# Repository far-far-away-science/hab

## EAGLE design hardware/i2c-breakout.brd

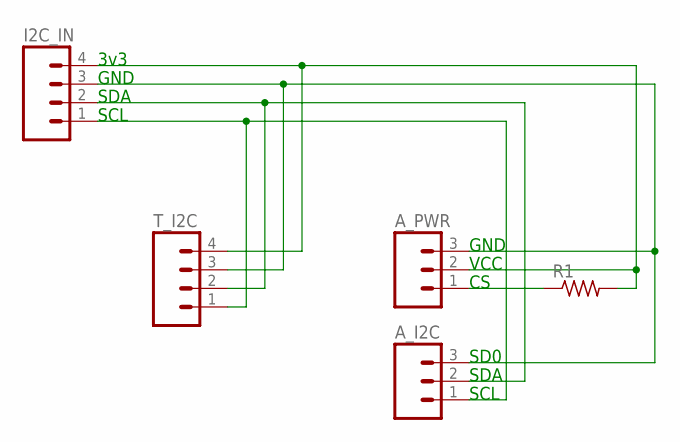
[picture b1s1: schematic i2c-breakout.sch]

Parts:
A_I2C: M03PTH; 1X03
A_PWR: M03PTH; 1X03
I2C_IN: M04PTH; 1X04
R1: R-US_0207/7; 0207/7
T_I2C: M04PTH; 1X04

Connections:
3V3: A_PWR.2, I2C_IN.4, R1.2, T_I2C.4
CS: A_PWR.1, R1.1
GND: A_I2C.3, A_PWR.3, I2C_IN.3, T_I2C.3
SCL: A_I2C.1, I2C_IN.1, T_I2C.1
SDA: A_I2C.2, I2C_IN.2, T_I2C.2

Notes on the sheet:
SCL
SDA
GND
3v3
SD0
VCC

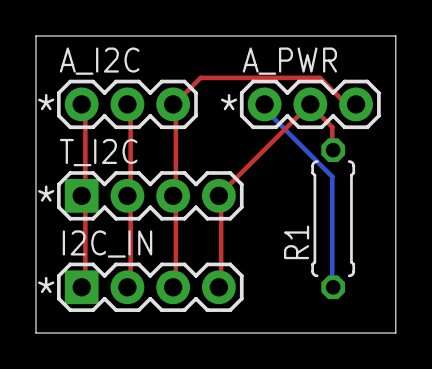
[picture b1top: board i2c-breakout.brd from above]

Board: 2 copper layers, 20.0 x 16.5 mm, 5 parts (0 on the bottom side), 5 nets.

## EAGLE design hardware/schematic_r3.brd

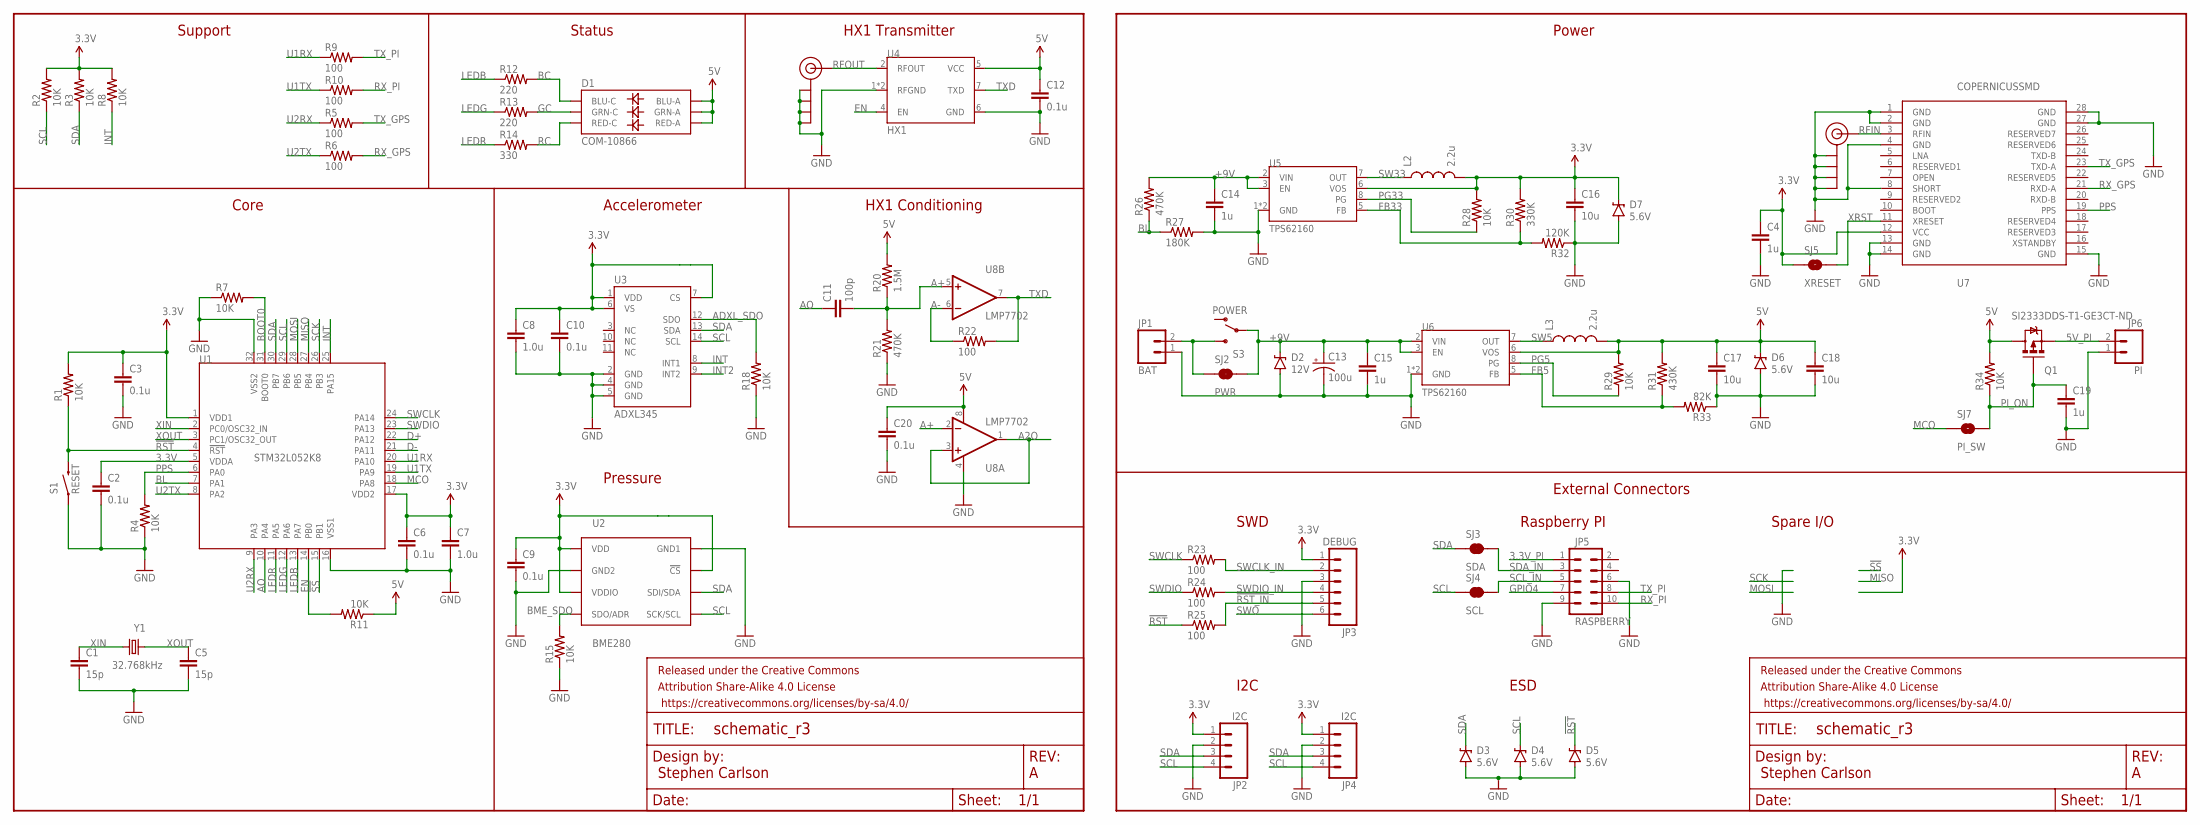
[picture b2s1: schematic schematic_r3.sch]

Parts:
C1, C5: 15p; 0805
C2, C3, C6, C9, C10, C12, C20: 0.1u; 0805
C4, C14, C15, C19: 1u; 0805
C7, C8: 1.0u; 0805
C11: 100p; 0805
C13: 100u; CPOL-RADIAL-10UF-25V
C16, C17, C18: 10u; 0805
D1: COM-10866; LED-TRICOLOR-5050
D2: 12V; SOD-323
D3, D4, D5, D6, D7: 5.6V; SOD-323
FRAME1, FRAME2: FRAME-LETTERNO_PACKAGE; DUMMY
J$1, J$2: SMA_EDGE; SMA-EDGE
JP1: BAT; 1X02
JP2, JP4: I2C; 1X04_LOCK
JP3: DEBUG; 1X06_LOCK
JP5: RASPBERRY; AVR_ICSP
JP6: PI; 1X02
L2, L3: 2.2u; 1008
Q1: SI2333DDS-T1-GE3CT-ND; SOT23-3
R1, R2, R3, R4, R7, R8, R11, R15, R18, R28, R29, R34: 10K; 0805
R5, R6, R9, R10, R22, R23, R24, R25: 100; 0805
R12, R13: 220; 0805
R14: 330; 0805
R20: 1.5M; 0805
R21, R26: 470K; 0805
R27: 180K; 0805
R30: 330K; 0805
R31: 430K; 0805
R32: 120K; 0805
R33: 82K; 0805
S1: RESET; TACTILE-PTH-THIN
S3: POWER; SWITCH-SPDT
SJ2: PWR; PAD-JUMPER-2-NC_BY_TRACE_YES_SILK
SJ3: SDA; PAD-JUMPER-2-NC_BY_TRACE_YES_SILK
SJ4: SCL; PAD-JUMPER-2-NC_BY_TRACE_YES_SILK
SJ5: XRESET; PAD-JUMPER-2-NO_YES_SILK
SJ7: PI_SW; PAD-JUMPER-2-NO_YES_SILK
U1: STM32L052K8; TQFP32-08
U2: BME280; BME280_LGA
U3: ADXL345; LGA14
U4: HX1; 1X12
U5, U6: TPS62160; MSOP8
U7: COPERNICUSSMD; COPERNICUS
U8: LMP7702; SO08
Y1: 32.768kHz; ABS25

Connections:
3.3V: C2.1, C3.1, C4.1, C6.1, C7.1, C8.1, C9.1, C10.1, C16.1, D7.C, JP2.1, JP3.1, JP4.1, L2.2, R1.2, R2.2, R3.2, R8.2, R28.2, R30.2, SJ5.1, U1.1 (VDD1), U1.5 (VDDA), U1.17 (VDD2), U2.P$2 (!CS), U2.P$6 (VDDIO), U2.P$8 (VDD), U3.1 (VDD), U3.6 (VS), U3.7 (CS), U5.6 (VOS), U7.12 (VCC)
3.3V_PI: JP5.1
5V: C12.1, C17.1, C18.1, C20.1, D1.1 (GRN-A), D1.2 (RED-A), D1.3 (BLU-A), D6.C, L3.2, Q1.3 (D), R11.1, R20.2, R29.2, R31.2, R34.2, U4.5 (VCC), U6.6 (VOS), U8.8 (V+)
5V_PI: JP6.2, Q1.2 (S)
!RST!: D5.C, R1.1, R25.1, S1.2, U1.4 (!RST!)
!RST_IN!: JP3.5, R25.2
!SS!: U1.15 (PB1)
+9V: C13.1 (+), C14.1, C15.1, D2.C, R26.2, S3.2, SJ2.2, U5.2 (VIN), U5.3 (EN), U6.2 (VIN), U6.3 (EN)
A2O: U8.1 (OUT), U8.3 (+IN)
A+: C11.2, R20.1, R21.2, U8.2 (-IN), U8.5 (+IN)
A-: R22.1, U8.6 (-IN)
ADXL_SDO: R18.2, U3.12 (SDO)
AO: C11.1, U1.10 (PA4)
BC: D1.4 (BLU-C), R12.2
BL: R26.1, R27.1, U1.7 (PA1)
BME_SDO: R15.2, U2.P$5 (SDO/ADR)
BOOT0: R7.2, U1.31 (BOOT0)
D+: U1.22 (PA12)
D-: U1.21 (PA11)
EN: R11.2, U1.14 (PB0), U4.4 (EN)
FB5: R31.1, R33.2, U6.5 (FB)
FB33: R30.1, R32.2, U5.5 (FB)
GC: D1.6 (GRN-C), R13.2
GND: C1.2, C2.2, C3.2, C4.2, C5.2, C6.2, C7.2, C8.2, C9.2, C10.2, C12.2, C13.2 (-), C14.2, C15.2, C16.2, C17.2, C18.2, C19.2, C20.2, D2.A, D3.A, D4.A, D5.A, D6.A, D7.A, J$1.GND@0 (GND), J$1.GND@1 (GND), J$1.GND@2 (GND), J$1.GND@3 (GND), J$2.GND@0 (GND), J$2.GND@1 (GND), J$2.GND@2 (GND), J$2.GND@3 (GND), JP1.1, JP2.2, JP3.3, JP4.2, JP5.6, JP5.9, JP6.1, R4.1, R7.1, R15.1, R18.1, R21.1, R27.2, R32.1, R33.1, S1.1, U1.16 (VSS1), U1.32 (VSS2), U2.P$1 (GND1), U2.P$7 (GND2), U3.2 (GND), U3.4 (GND), U3.5 (GND), U4.1 (RFGND), U4.3 (RFGND), U4.6 (GND), U5.1 (GND), U5.4 (GND), U6.1 (GND), U6.4 (GND), U7.1 (GND), U7.2 (GND), U7.4 (GND), U7.8 (SHORT), U7.13 (GND), U7.14 (GND), U7.15 (GND), U7.27 (GND), U7.28 (GND), U8.4 (V-)
GPIO4: JP5.7
INT: R8.1, U1.25 (PA15), U3.8 (INT1)
INT2: U3.9 (INT2)
LEDB: R12.1, U1.13 (PA7)
LEDG: R13.1, U1.12 (PA6)
LEDR: R14.1, U1.11 (PA5)
MCO: SJ7.1, U1.18 (PA8)
MISO: U1.27 (PB4)
MOSI: U1.28 (PB5)
PG5: R29.1, U6.8 (PG)
PG33: R28.1, U5.8 (PG)
PI_ON: C19.1, Q1.1 (G), R34.1, SJ7.2
PPS: R4.2, U1.6 (PA0), U7.19 (PPS)
RC: D1.5 (RED-C), R14.2
RFIN: J$2.SIG (SIGNAL), U7.3 (RFIN)
RFOUT: J$1.SIG (SIGNAL), U4.2 (RFOUT)
RX_GPS: R6.2, U7.21 (RXD-A)
RX_PI: JP5.10, R10.2
SCK: U1.26 (PB3)
SCL: D4.C, JP2.4, JP4.4, R2.1, SJ4.1, U1.29 (PB6), U2.P$4 (SCK/SCL), U3.14 (SCL)
SCL_IN: JP5.5, SJ4.2
SDA: D3.C, JP2.3, JP4.3, R3.1, SJ3.1, U1.30 (PB7), U2.P$3 (SDI/SDA), U3.13 (SDA)
SDA_IN: JP5.3, SJ3.2
SW5: L3.1, U6.7 (OUT)
SW33: L2.1, U5.7 (OUT)
SWCLK: R23.1, U1.24 (PA14)
SWCLK_IN: JP3.2, R23.2
SWDIO: R24.1, U1.23 (PA13)
SWDIO_IN: JP3.4, R24.2
SWO: JP3.6
TXD: R22.2, U4.7 (TXD), U8.7 (OUT)
TX_GPS: R5.2, U7.23 (TXD-A)
TX_PI: JP5.8, R9.2
U1RX: R9.1, U1.20 (PA10)
U1TX: R10.1, U1.19 (PA9)
U2RX: R5.1, U1.9 (PA3)
U2TX: R6.1, U1.8 (PA2)
VIN: JP1.2, S3.3 (S), SJ2.1
XIN: C1.1, U1.2 (PC0/OSC32_IN), Y1.1
XOUT: C5.1, U1.3 (PC1/OSC32_OUT), Y1.4 (2)
XRST: SJ5.2, U7.11 (XRESET)

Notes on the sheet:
Stephen Carlson
External Connectors
SWD
Raspberry PI
Spare I/O
Support
Status
HX1 Transmitter
Core
Accelerometer
Pressure
HX1 Conditioning
I2C
ESD
Power

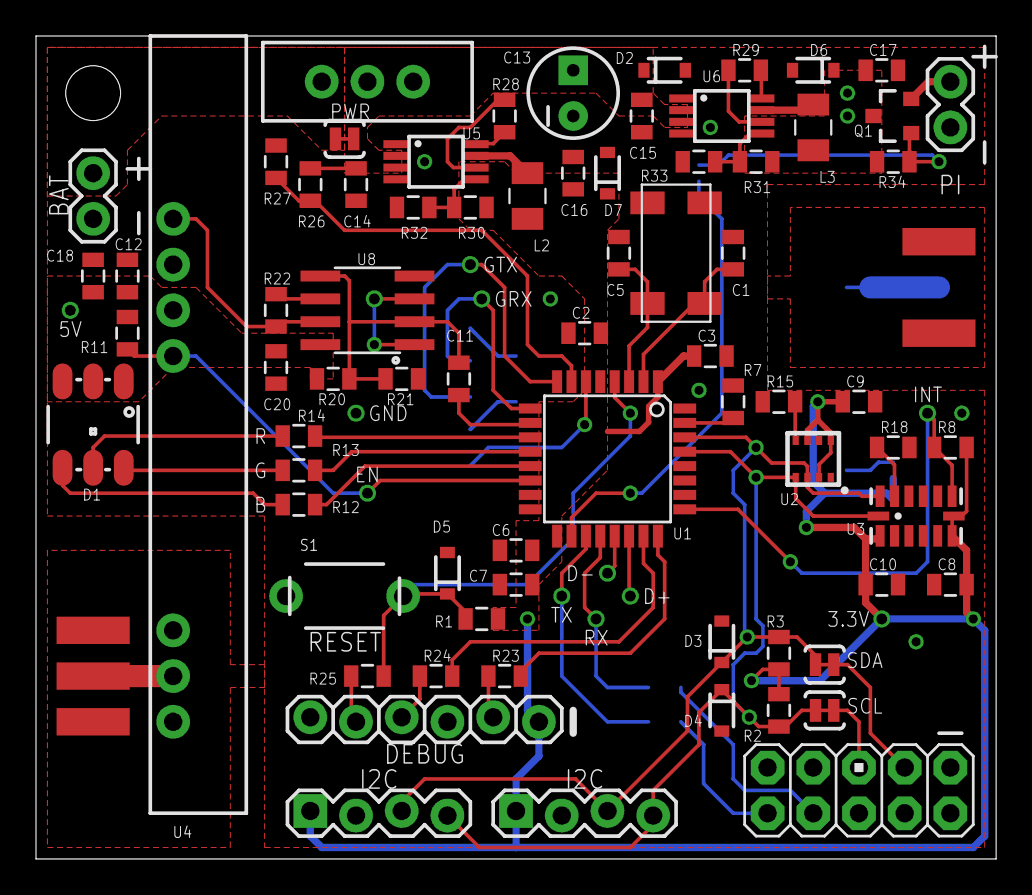
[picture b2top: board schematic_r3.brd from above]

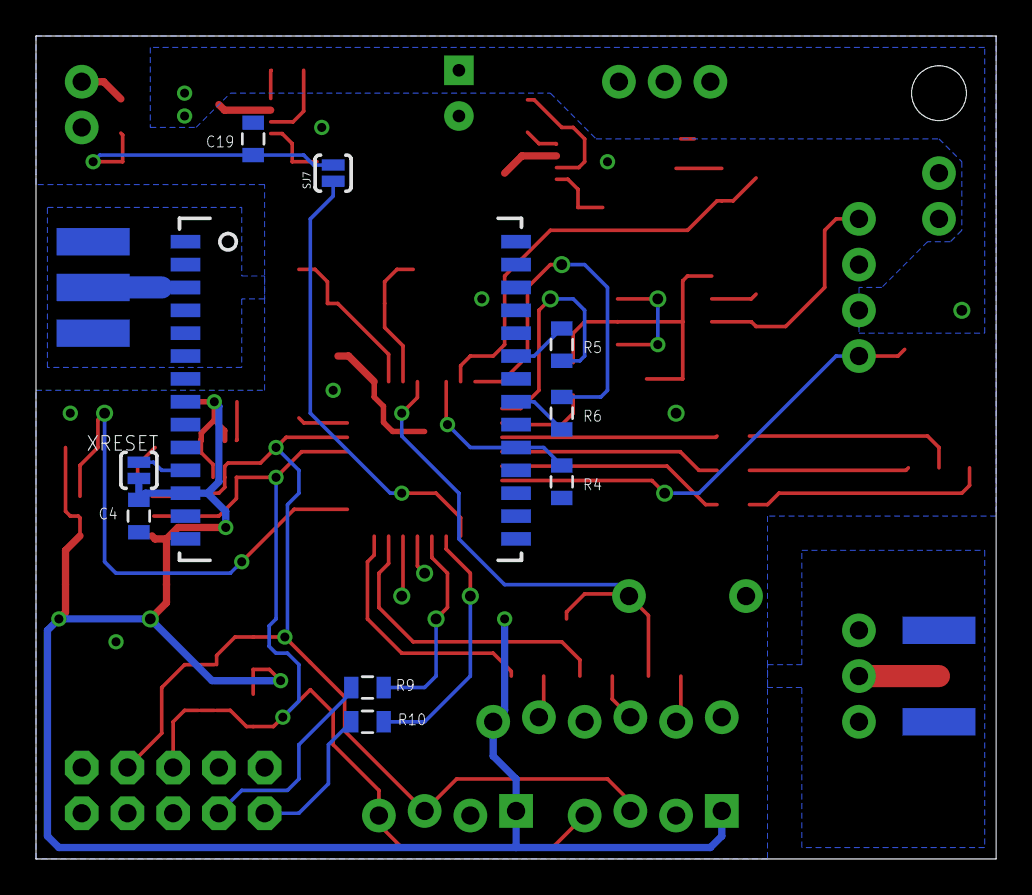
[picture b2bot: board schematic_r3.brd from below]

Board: 2 copper layers, 53.3 x 45.7 mm, 87 parts (11 on the bottom side), 55 nets.

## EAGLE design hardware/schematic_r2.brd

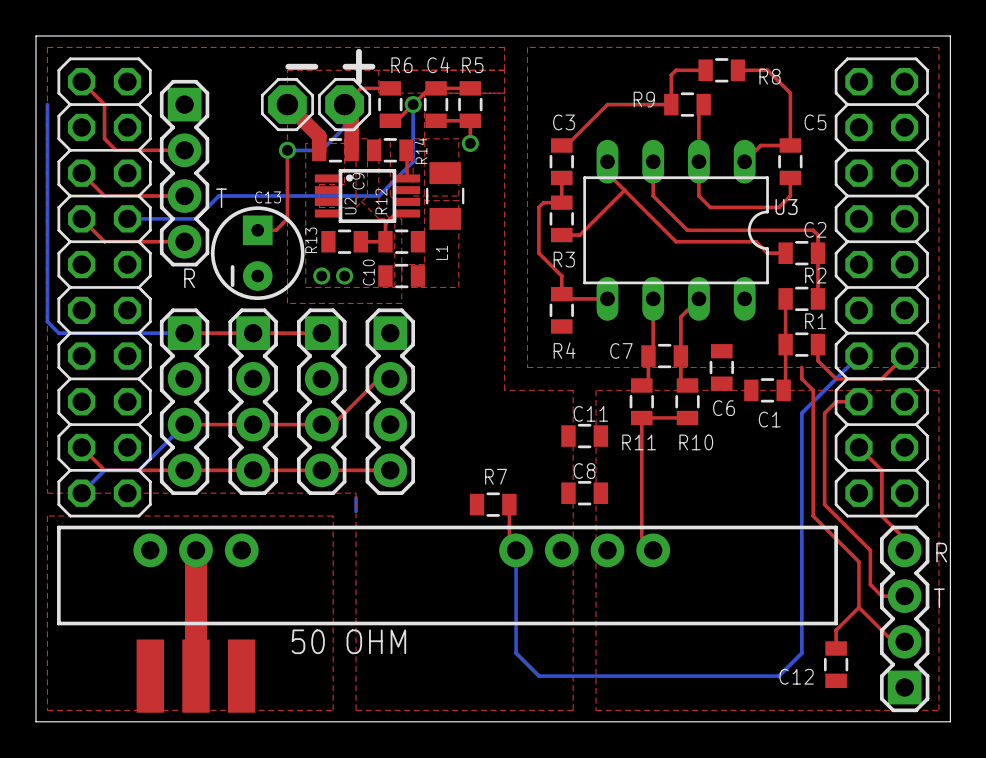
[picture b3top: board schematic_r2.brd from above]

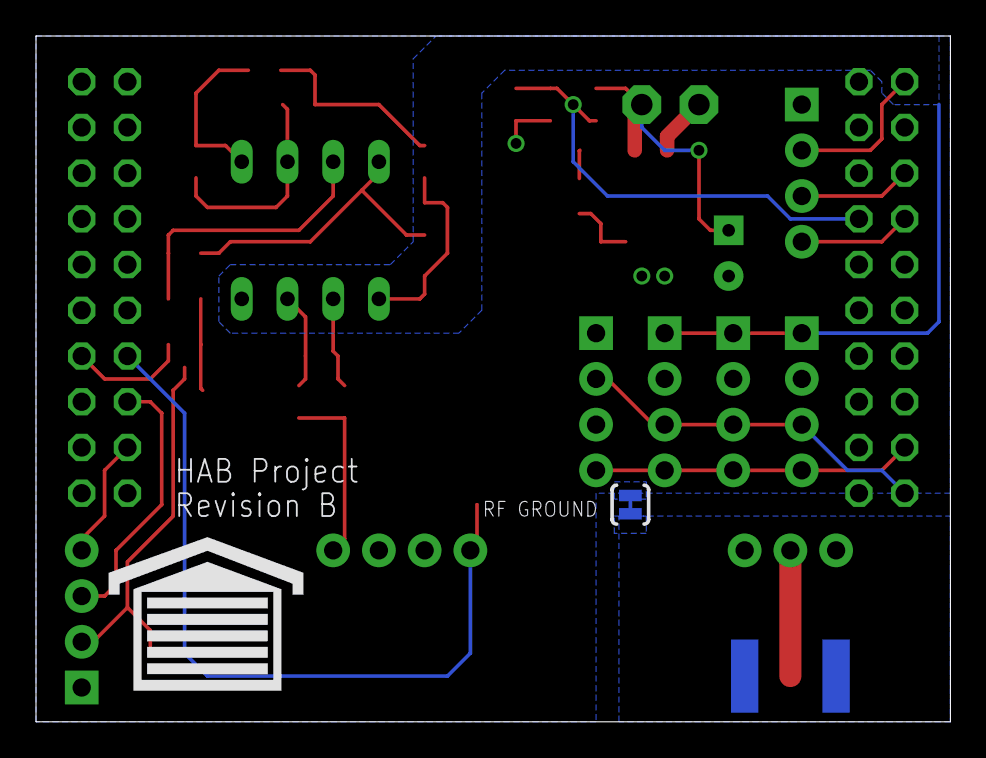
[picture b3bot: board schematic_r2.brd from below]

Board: 2 copper layers, 50.8 x 38.1 mm, 45 parts (2 on the bottom side), 27 nets.

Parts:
C1: 47nF; 0805
C2, C3: 100pF; 0805
C4, C6, C8, C12: 0.1uF; 0805
C5, C7: 10pF; 0805
C9, C10, C11: 10u; 0805
C13: 68u; CPOL-RADIAL-10UF-25V
FRAME1: FRAME-LETTERNO_PACKAGE; DUMMY
J1: SMA_EDGE; SMA-EDGE
JP1: I2C IN; 1X04
JP2, JP5, JP6: SENSORS; 1X04
JP3: VENUS; 1X04
JP4: COPERNICUS; 1X04
L1: 2.2u; 1008
R1: 1K; 0805
R2, R3, R6: 470K; 0805
R4: 1.5M; 0805
R5: 180K; 0805
R7: 2.2K; 0805
R8, R10: 100; 0805
R9, R11, R14: 100K; 0805
R12: 430K; 0805
R13: 82K; 0805
SJ1: JUMPER-PAD-2-NC_BY_TRACE; PAD-JUMPER-2-NC_BY_TRACE_YES_SILK
TIVA_1, TIVA_2: 2X10
TP1, TP2: MCS08
U1: HX1; 1X12
U2: TPS62160; MSOP8
U3: LMC6482; DIL08
U$1: GARAGE

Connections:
+3V3: C6.1, C12.1, JP2.1, JP3.2, JP4.2, JP5.1, JP6.1, R4.2, TIVA_1.1, U3.8
+5V: C8.1, C10.1, C11.1, JP1.1, L1.2, R7.2, R12.2, R14.2, TIVA_1.2, U1.5, U2.6
+9V: C9.1, C13.1, R6.2, TP1.MP, U2.2, U2.3
CRX: JP4.4, TIVA_2.17
CTX: JP4.3, TIVA_2.15
EN: R7.1, TIVA_2.13, U1.4
FB5: R12.1, R13.2, U2.5
GNDA: C1.2, C2.2, C4.2, C6.2, C8.2, C9.2, C10.2, C11.2, C12.2, C13.2, JP1.3, JP2.2, JP3.1, JP4.1, JP5.2, JP6.2, R3.1, R5.1, R13.1, SJ1.1, TIVA_1.4, TIVA_2.2, TP2.MP, U1.6, U2.1, U2.4, U3.4
HPFB: C7.2, R11.1, U3.6
HPIN: C3.1, R8.2, R9.2
HPOUT: C3.2, R3.2, R4.1, U3.5
LPFB: C5.2, R9.1, U3.2
LPOUT: C5.1, R8.1, U3.1
PG5: R14.1, U2.8
PWMF1: C1.1, R1.2, R2.1
PWMF2: C2.1, R2.2, U3.3
PWMOUT: R1.1, TIVA_2.14
RFGND: J1.GND@0, J1.GND@1, J1.GND@2, J1.GND@3, SJ1.2, U1.1, U1.3
RFOUT: J1.SIG, U1.2
SCL: JP1.4, JP2.4, JP5.4, JP6.4, TIVA_1.17
SDA: JP1.2, JP2.3, JP5.3, JP6.3, TIVA_1.19
SW5: L1.1, U2.7
TXD: R10.2, R11.2, U1.7
TXF: C7.1, R10.1, U3.7
VBAT: C4.1, R5.2, R6.1, TIVA_1.8
VRX: JP3.4, TIVA_1.7
VTX: JP3.3, TIVA_1.5

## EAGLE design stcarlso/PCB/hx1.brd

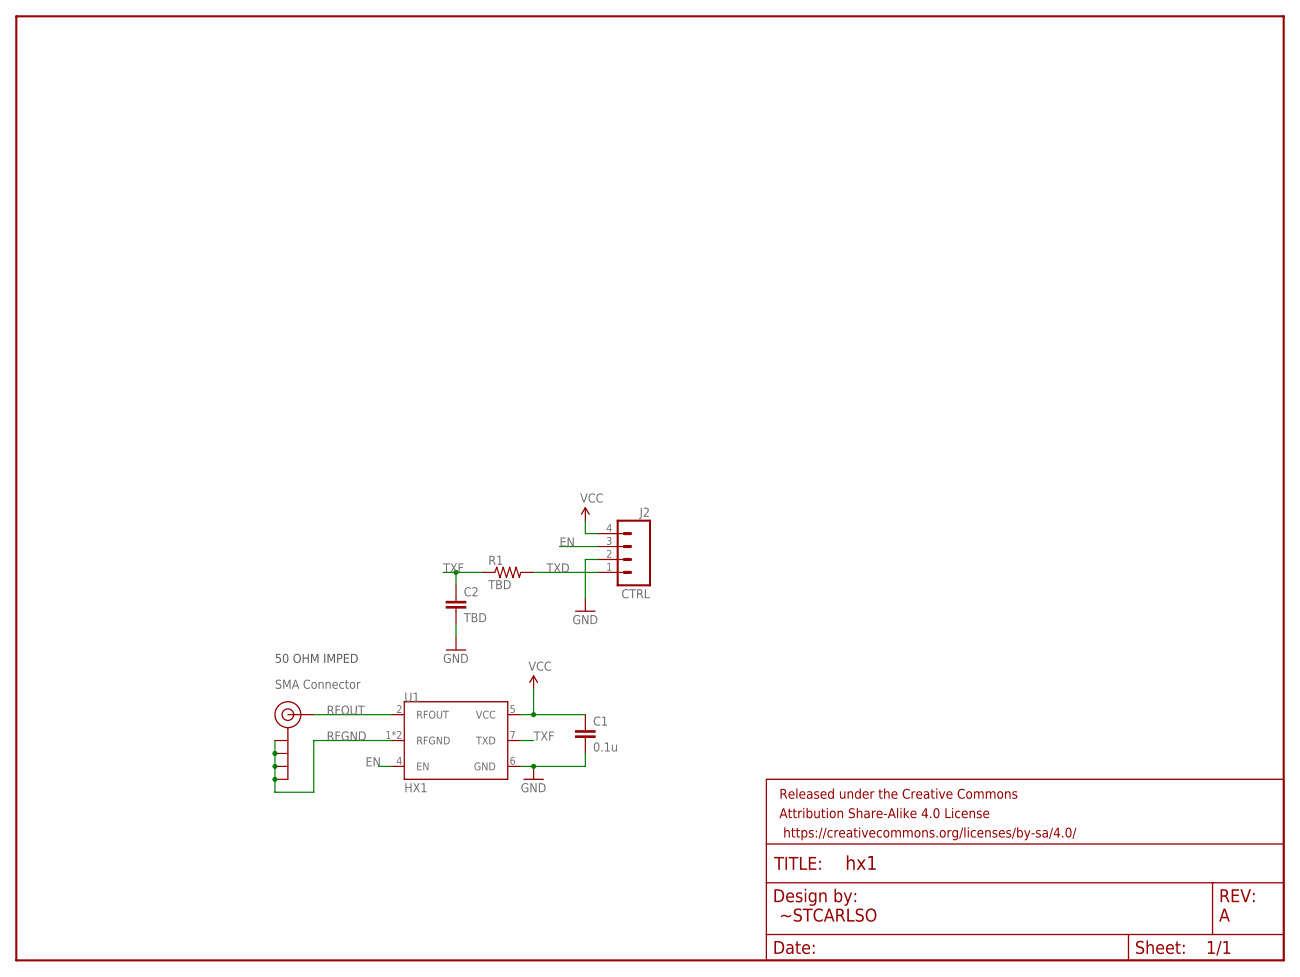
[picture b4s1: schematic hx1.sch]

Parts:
C1: 0.1u; CAP-PTH-SMALL
C2: TBD; CAP-PTH-SMALL
FRAME1: FRAME-LETTERNO_PACKAGE; DUMMY
J1: SMA_EDGE; SMA-EDGE
J2: CTRL; 1X04
R1: TBD; AXIAL-0.3
U1: HX1; 1X12

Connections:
EN: J2.3, U1.4 (EN)
GND: C1.2, C2.2, J2.2, U1.6 (GND)
RFGND: J1.GND@0 (GND), J1.GND@1 (GND), J1.GND@2 (GND), J1.GND@3 (GND), U1.1 (RFGND), U1.3 (RFGND)
RFOUT: J1.SIG (SIGNAL), U1.2 (RFOUT)
TXD: J2.1, R1.P$2 (2)
TXF: C2.1, R1.P$1 (1), U1.7 (TXD)
VCC: C1.1, J2.4, U1.5 (VCC)

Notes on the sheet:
SMA Connector
50 OHM IMPED
~STCARLSO

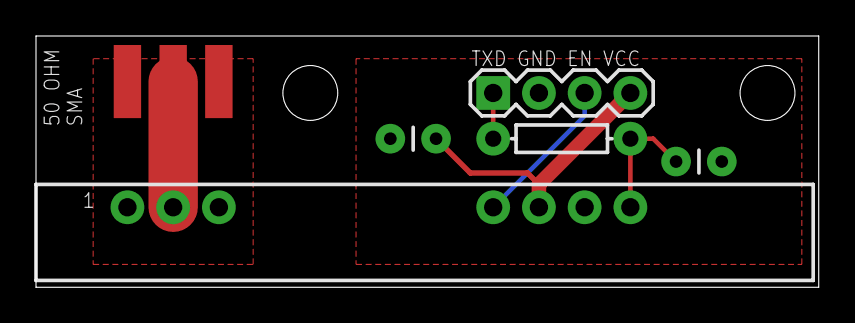
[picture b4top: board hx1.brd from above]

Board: 2 copper layers, 43.5 x 14.0 mm, 7 parts (0 on the bottom side), 7 nets.

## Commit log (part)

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2015-05-25 adding working skeleton for GPS -> Radio
2015-05-25 fixed compiling errors
2015-05-26 started actual work for venus GPS (added skeleton for UART interrupt handling)
2015-05-26 added code to read data from UART to the buffer
2015-05-27 implemented read ring-buffer
2015-05-28 added ability to read venus GPS messages
2015-05-28 added simpler/shorter message for APRS transmission
2015-05-31 added support for working with several UARTs simulataneously
2015-06-01 added write UART library (need to think about concurrency issues)
2015-06-01 added missing project files
2015-06-04 added debug uart port configuration
2015-06-12 added single-flat rotating buffer for uart write functions (will need for debugging)
2015-06-12 fixed spaces/tabs (screwed up after reinstalling keil)
2015-06-16 added PWM modulation (still need to add APRS message formatting and FCR/CRC encoding)
2015-06-16 missing files (as usuall forgot to close IDEs)
2015-06-16 added skeleton project for uart-driver
2015-06-16 moved gps-radio project out of my own space to common space
2015-06-16 moved uart driver to common space
2015-06-17 Add very basic schematic and PCB for proper mounting and impedance matching of the HX1. RF output trace to edge launch SMA connector is 50 ohms single ended.
2015-06-17 added tools to enable/disable tracing (to help in driver development)
2015-06-18 Update PCB to include pads for RC filter (values TBD)
2015-06-18 Update PCB footprint of HX1 with tighter dimensions
2015-06-18 added pre-emphasis, added a bit of code for UART driver (fails to create device though)
2015-06-19 reformatting APRS code to make it a bit faster
2015-06-19 added APRS messages encoding (still no luck with decoding, need to investigate futher)
2015-06-19 Fix PCB silkscreen
2015-06-20 fixed several bugs in APRS message encoding and transport
2015-06-24 improved PWM -> AX.25 AFSK signal generation (still not 100% for cases where I switch frequencies)
2015-06-26 made AFSK generation even better
2015-06-26 plain modem is now working fine, need to fix AFSK for AX.25 now
2015-06-27 cleaned up aprs code a bit, made it work without hacks
2015-06-27 added some todos, returned 30s delay for APRS messages
2015-06-28 Add untested I2C code to Tiva project. No guarantee that it works, this commit is to stop the conflicts over gitignore and the project file...
2015-06-28 Add Raspberry PI 2 Windows 10 application intended to view the I2C/UART data from the telemetry board. Currently a headed application which displays the information.
2015-06-28 The code can obtain a GPS lock, parse it, load lat + lon into the I2C registers, and successfully transfer/decode it to the Raspberry PI 2!
2015-06-28 Fix author of previous commit
2015-06-30 fixed driver inf file, now driver can be installed and creates without errors
2015-06-30 added more code for UART driver (filling in device methods)
2015-07-01 added hardware initialiation for UART driver
2015-07-01 Update I2C protocol to major 2, which supports altitude, fixes heading, adds satellite count/fix available, and transmits both GPS modules
2015-07-02 GPSFetch no longer reads data from the same bank for all index values. Therefore, GPS #1 actually works.
2015-07-03 refactored code into more or less standard UART and into BCM2836 miniuart
2015-07-03 Created HABService, the headless background task which logs configured sensor data to a log file in the C:\Users\DefaultAccount\Downloads folder on the Raspberry PI 2. Currently supports telemetry MC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
2015-07-04 Fix race condition on multiple sensor polling at the same time. Release builds are still randomly crashing when set as startup application, but debug builds appear to work better.
2015-07-06 added a bit of controlled initialization code
2015-07-06 added todo signs to distinguish which methods I need to work on 1st
2015-07-06 Upgrade both Pi apps to the 10158 Windows 10 SDK (compatible with the latest internal 10160 image released to the 1506 share, may need a hack to get an older debugger version). Increase details in er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
2015-07-06 added PowerEvtD0Entry implementation
2015-07-06 added UartInterruptEvtInterruptEnable implementation, removed uneccessary function
2015-07-06 almost finished device power on/off procedures (need to think about error events logging)
2015-07-06 added enabled/disable of UART device, added todos in places where I have to do ETW logging, added todos into unfinished method
2015-07-06 added logging for uart errors, full power off/on/off/... cycle seeme to be working fine
2015-07-07 a bit of refactoring and bug hunting, trying to figure out why my SerCx2 doesn't seem to be working
2015-07-07 added device instance id query, still no luck on any of the interrupts
2015-07-08 Further increase to debug spew to drill down root cause of sampling errors. Blink green LED periodically in Tiva application to indicate transactions are alive, and go into low power mode.
2015-07-08 removed uart project (need to refactor code quite a bit, move it around)
2015-07-08 adding uart-driver back, with heavily refactored structure. still need to refactor code,
2015-07-08 Further attempts to increase HABService reliability by not opening and closing the I2C handles on each sample.
2015-07-08 huge refactoring of code to allow more or less customizable drivers for different hardware
2015-07-08 LED changes unintentionally (would have) broken APRS, fix conflict over the PWM system divider
2015-07-13 fixes to radio MCU, added turn on green/red on isr fault
2015-07-14 added test app for UART driver testing
2015-07-15 added a bit of pl011 code, added voltage and cpu temperature telemetry to tiva-c code
2015-07-15 added more uart code (still problems with interrupts)
2015-07-15 fixed registers read/write
2015-07-17 added schematic draft
2015-07-18 added a bit of more parts to op-amp (trying to reduce the noise)
2015-07-18 added schematics to disable unused op-amp
2015-07-18 fixed R9 wiring, added capacitor for power
2015-07-19 now utilizing opamp to separate high pass filter from hx1
2015-07-26 My first take on the complete PCB (if we want to make it). No vias, traces on one side only (+ ground plane), should dimensionally match the Tiva (1::1 print to make sure!)
2015-07-27 Add missing dependencies from previous commit.
2015-07-27 Move background task deferral as suggested by IoT dev Jordan Rhee to avoid startup crash
2015-08-01 Bugfix in status LED reporting to avoid using PWM if not configured
2015-08-01 Fix a few ERC violations on PCB (C4 still needs a value) and perform mass silkscreen cleanup.
2015-08-01 Rebuild project again for the public (released) driver/VS builds. Still fails on release builds.
2015-08-02 Fix bug with I2C interupts not being enabled, introduced by 6cc2243c.
2015-08-02 Fix contention over the log file which was the actual root cause of HABService instability
2015-08-12 Update PCB to include VRM module, change all components to 0805, and upgrade silkscreen
2015-08-12 Add another cool logo for testing purposes
2015-08-16 Implement TMP102 temperature logging in HABService
2015-08-22 Add watchdog timer functionality and blink heartbeat LED. Now autorecovers on failures, fixes #1.
2015-08-22 Add dithering for APRS transmit interval to avoid potential phase mismatches with other repeating message sources
2015-08-22 Put Copernicus GPS into AIR mode. Fixes #7, but needs testing.
2015-08-23 Voltage and temperature data is now saved to EEPROM every 30 seconds. This mode must be activated by holding down SW1 during power up or reset, otherwise the EEPROM will not be modified to allow data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
    C# application development is in progress to allow EEPROM readout over I2C.
2015-08-24 Add EEPROM reader application for data stored on telemetry MCU
2015-08-27 added breadboard schematics
2015-08-27 added uap/iot library to driver test app project
2015-08-28 added enable/disable HX1 code, fixed (I hope) APRS message syntax
2015-08-29 Add a script which parses the massive log files and can pare them down to smaller data sets. Also add a sample data run [yes, it was taken while standing still, but is within reason]
    Added connections for I2C and temperature sensor to breadboard schematic. Should fix #11 unless there is more to be added.
2015-09-03 Fix issue #12 - Press SW1 to send APRS message immediately Blink blue LED when APRS message is being sent
2015-09-07 Fix pad to pad spacing on the "1008" inductor (not really) on the PCB. Existing board works, but is vulnerable to tombstoning if reflowed
2015-09-11 fixed a bug where pulse width wasn't qualculated properly (used int value instead of float)
2015-09-13 changed breadboard to reflect PCB design
2015-09-15 added trig tables (seems to be the most reliable way but they consume a lot of memory and we are very close to 32K Keil limit)
2015-09-15 added readme.txt with description of macroses used for project customization
2015-09-15 moved hardware specific code out of APRS, fixed signal method names
2015-09-16 fixed APRS message format (need to work on payload)
2015-09-16 moved to use cosign sign table instead of cosign values, added comments for SSIDs, fixed some typos
2015-09-17 added ability to dump gps/telemetry to UART, now bundled up nmea messages will be split and processed one at a time
2015-09-18 added headers to debug messages, fixed debug messages initialization
2015-09-20 - changed nmea parsing as messages have different precision and it wasn't working - fixed bugs in write uart - fixed i2c data copy bugs for copernicus (was overriding venus gps data due to invalid po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
2015-09-20 - added specs to repository - fixed some warnings - added manual input gps fix mode to supported list and fixed unit tests - added raspberry pi connection to breadboard schematic
2015-09-20 - added GPS and speed/track to APRS messages - fixed some small issues in nmea messages parsing
2015-09-20 fixed bug in parseFloat
2015-09-21 added telemetry message sequential id
2015-09-21 Fixed #20: i2c service shouldn't bail if one device isn't present
2015-09-21 added more specs and manuals
2015-09-25 fixed telemetry message bug
2015-09-25 minor cleanup
2015-09-29 fixed invalid encoding of latitude/longitude for telemetry board
2015-10-01 added a bit of comments for nmea code
2015-10-01 refactoring nmea
2015-10-09 Fix #25: add accelerometer code to Raspberry PI (through I2C)
2015-10-10 fixed release build and appx package creation
2015-10-10 added PCB / schematics revision 2
2015-10-11 Fixed #5: Need to send APRS messages more frequently on descend closer to the ground; Fixed #22: cleanup main.c
2015-10-13 refactored nmea and added tests for it
2015-10-14 moved stuff around a bit, preparing to add tests for aprs
2015-10-14 added accelerometer schematics (for breadboard)
2015-10-14 added some tests for aprs, still need more
2015-10-18 fixed TX RX naming for copernicus (was swapped), fixed AX.25 PWM output port to correct one
2015-10-19 fixed APRS time message format
2015-10-20 Fixed #35: Raspberry PI should have successful startup indicator. -- LED is constant green after boot, and only blinks when I2C communication begins
2015-10-22 Fixed #26: fix PCB bugs in Revision 2 schematics and board
    Note that subsequent flights should really use an STM32-based telemetry board to get better power usage and weight.
2015-10-23 added tests for create packet payload
2015-10-26 added i2c breakout board
2015-10-28 Start work on second generation telemetry MCU board. Only 6 batteries, more reliable, smaller, and lighter!
2015-11-02 Update r3 schematics and board to fix minor issues
2015-11-12 added images for wiki
2015-11-12 fixed image for wiki
2015-11-14 removed copernicus configuration code (it was on wrong UART and I set it up using tool provided manufacturer)
2016-02-27 EEPROMReader and HABService now compile against the 10586 (TH2) OS and SDK.
2016-03-28 commiting last changes I made before launch
2016-03-28 moved v1 code to v1 folder
2016-03-28 moved images back to root as they are used in wikis, added weather report for launch day
2016-03-30 n6udp info
2016-04-02 kml and merge script
2016-04-02 animations for v1

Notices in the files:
parts and their libraries:
SparkFun-Connectors: Licensing: Creative Commons ShareAlike 4.0 International - https://creativecommons.org/licenses/by-sa/4.0
SparkFun-Aesthetics: Released under the Creative Commons Attribution Share-Alike 4.0 License
SparkFun-Aesthetics: https://creativecommons.org/licenses/by-sa/4.0
